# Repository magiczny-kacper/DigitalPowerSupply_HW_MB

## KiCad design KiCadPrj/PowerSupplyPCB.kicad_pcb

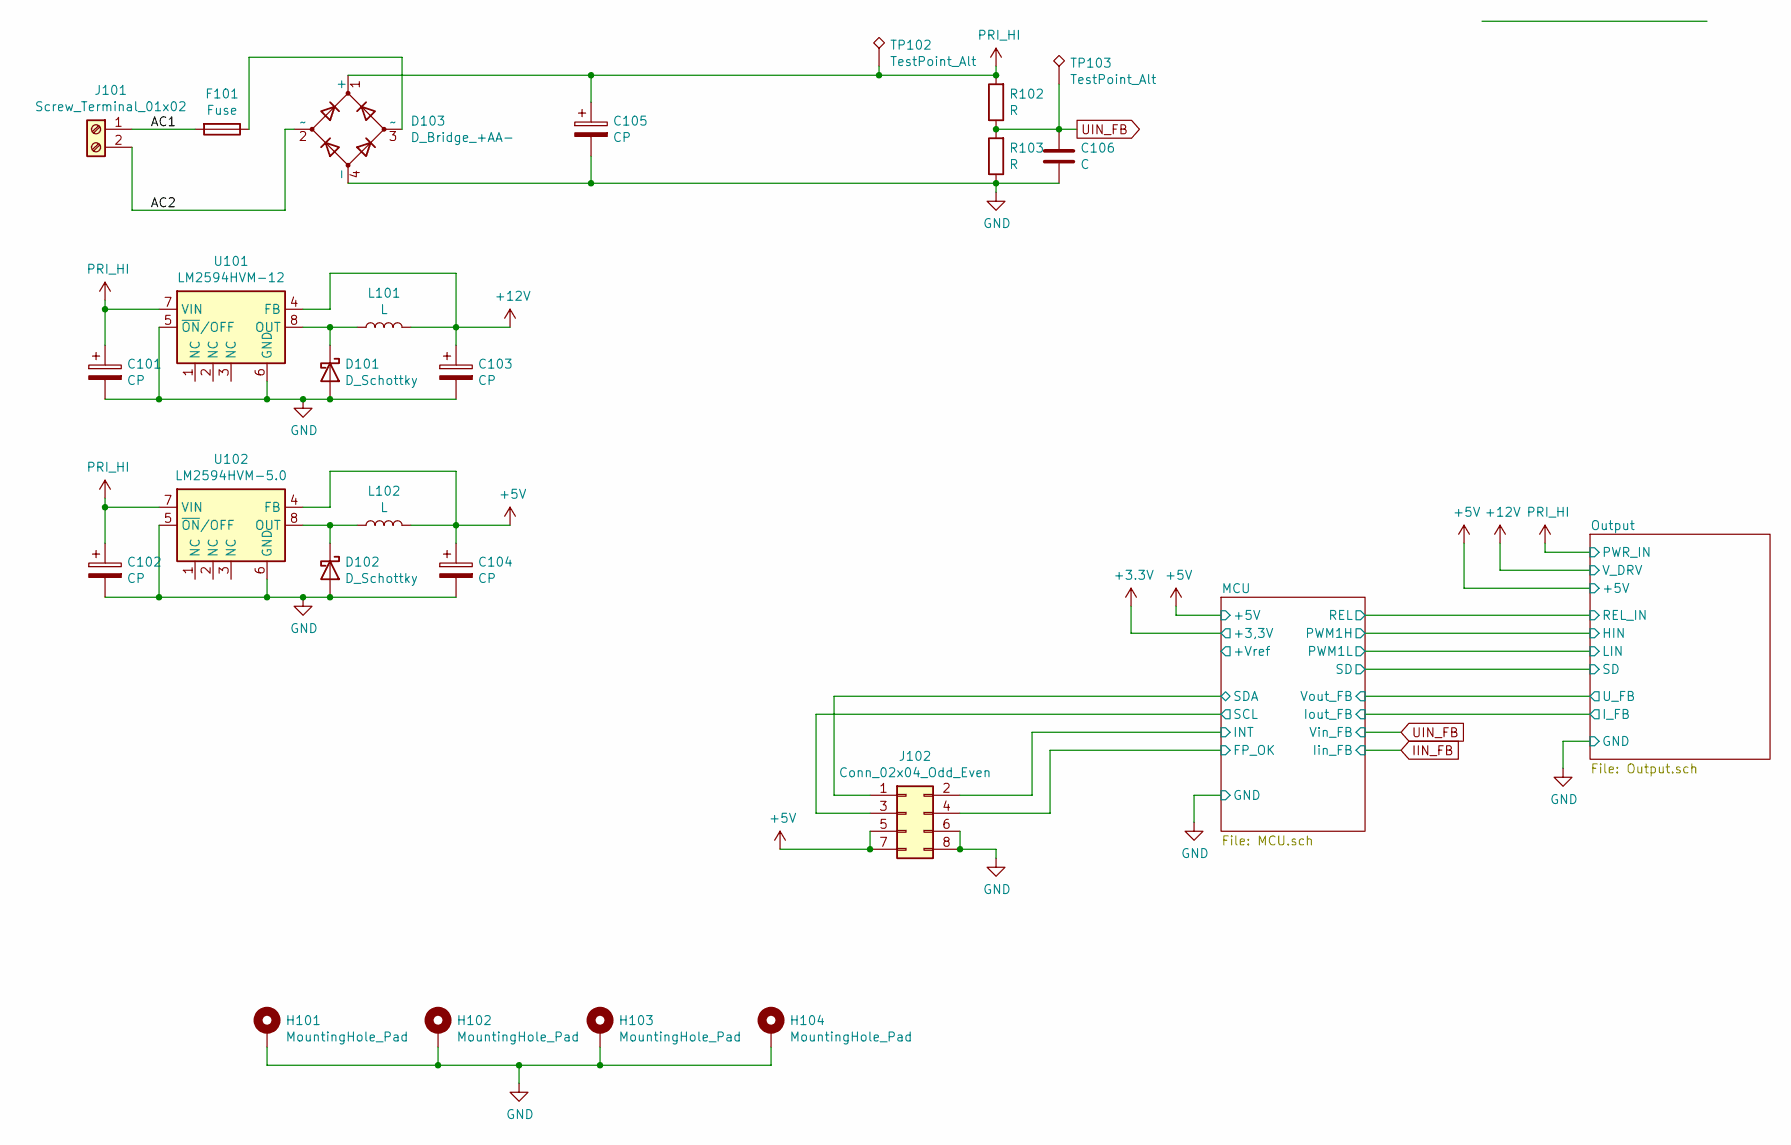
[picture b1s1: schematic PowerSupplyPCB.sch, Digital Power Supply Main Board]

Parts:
C101, C102, C103, C104: CP; CP_Elec_5x3.9
C105: CP; CP_Radial_D22.0mm_P10.00mm_SnapIn
C106: C; C_0805_2012Metric
D101, D102: D_Schottky; D_SMA
D103: D_Bridge_+AA-; Diode_Bridge_Vishay_KBU
F101: Fuse; Fuseholder_Cylinder-5x20mm_EATON_HBW_Vertical_Closed
H101, H102, H103, H104: MountingHole_Pad; MountingHole_3.2mm_M3_Pad_Via
J101: Screw_Terminal_01x02; PhoenixContact_MSTBVA_2,5_2-G-5,08_1x02_P5.08mm_Vertical
J102: Conn_02x04_Odd_Even; IDC-Header_2x04_P2.54mm_Vertical
L101, L102: L; L_Bourns_SRN8040TA
R102, R103: R; R_0805_2012Metric
TP102, TP103: TestPoint_Alt; TestPoint_Pad_3.0x3.0mm
U101: LM2594HVM-12; SOIC-8_3.9x4.9mm_P1.27mm
U102: LM2594HVM-5.0; SOIC-8_3.9x4.9mm_P1.27mm

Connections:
+5V: C104.1, J102.5, J102.7, L102.2, U102.4 (FB); also elsewhere on the board
+12V: C103.1, L101.2, U101.4 (FB); also elsewhere on the board
/AC1: F101.2, J101.1
/AC2: D103.2 (~~), J101.2
/MCU/FP_OK: J102.4; also elsewhere on the board
/MCU/INT: J102.2; also elsewhere on the board
/MCU/SCL: J102.3; also elsewhere on the board
/MCU/SDA: J102.1; also elsewhere on the board
GND: C101.2, C102.2, C103.2, C104.2, C105.2, C106.1, D101.2 (A), D102.2 (A), D103.4 (-), H101.1, H102.1, H103.1, H104.1, J102.6, J102.8, R103.1, U101.5 (~ON~/OFF), U101.6 (GND), U102.5 (~ON~/OFF), U102.6 (GND); also elsewhere on the board
unnamed: D101.1 (K), L101.1, U101.8 (OUT)
unnamed: D102.1 (K), L102.1, U102.8 (OUT)
unnamed: D103.3 (~~), F101.1
PRI_HI: C101.1, C102.1, C105.1, D103.1 (+), R102.2, TP102.1, U101.7 (VIN), U102.7 (VIN); also elsewhere on the board
UIN_FB: C106.2, R102.1, R103.2, TP103.1; also elsewhere on the board

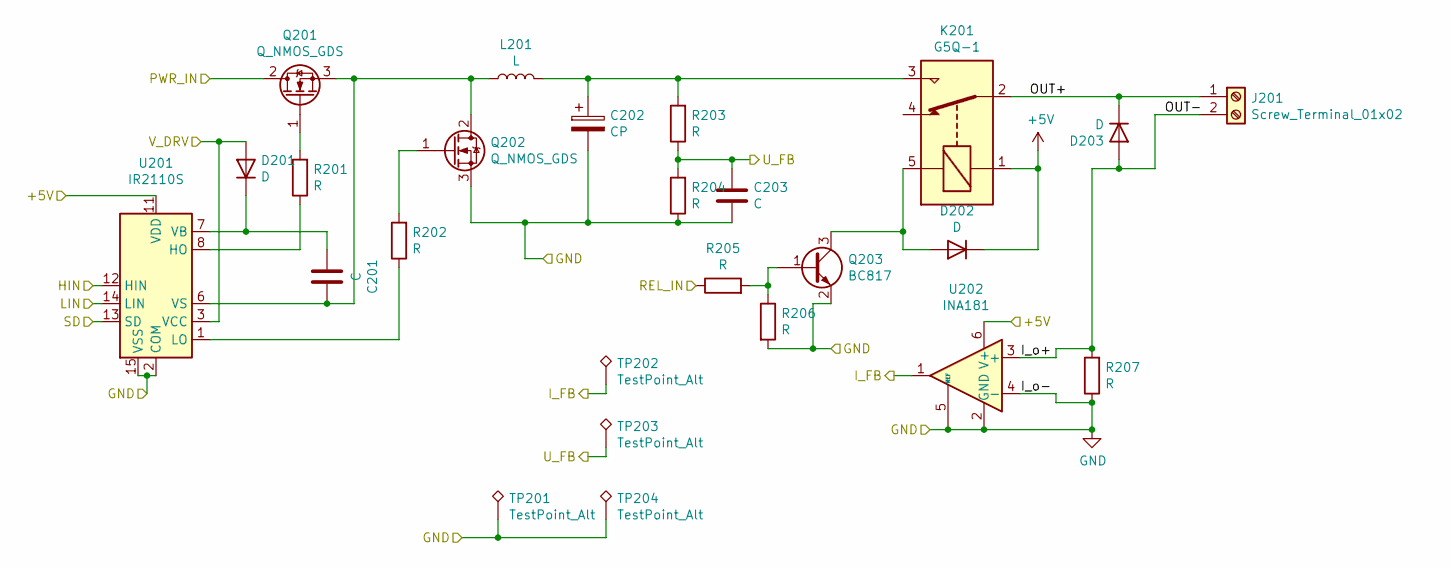
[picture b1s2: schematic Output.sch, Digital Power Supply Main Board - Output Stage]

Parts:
C201, C203: C; C_0805_2012Metric
C202: CP; CP_Radial_D22.0mm_P10.00mm_SnapIn
D201, D202, D203: D; D_SMA
J201: Screw_Terminal_01x02; PhoenixContact_MSTBVA_2,5_2-G-5,08_1x02_P5.08mm_Vertical
K201: G5Q-1; Relay_SPDT_Omron-G5Q-1
L201: L; WE_74437529203331
Q201, Q202: Q_NMOS_GDS; TO-220-3_Vertical
Q203: BC817; SOT-23
R201, R202, R203, R204, R205, R206: R; R_0805_2012Metric
R207: R; R_2512_6332Metric
TP201, TP202, TP203, TP204: TestPoint_Alt; TestPoint_Pad_3.0x3.0mm
U201: IR2110S; SOIC-16W_7.5x10.3mm_P1.27mm
U202: INA181; SOT-23-6

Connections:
+5V: D202.1 (K), K201.1, U201.11 (VDD), U202.6 (V+); also elsewhere on the board
+12V: D201.2 (A), U201.3 (VCC); also elsewhere on the board
/MCU/REL: R205.1; also elsewhere on the board
/MCU/SD: U201.13 (SD); also elsewhere on the board
/Output/HIN: U201.12 (HIN); also elsewhere on the board
/Output/I_FB: TP202.1, U202.1; also elsewhere on the board
/Output/I_o+: D203.2 (A), J201.2, R207.2, U202.3 (+)
/Output/LIN: U201.14 (LIN); also elsewhere on the board
/Output/OUT+: D203.1 (K), J201.1, K201.2
/Output/U_FB: C203.2, R203.1, R204.2, TP203.1; also elsewhere on the board
GND: C202.2, C203.1, Q202.3 (S), Q203.2 (E), R204.1, R206.2, R207.1, TP201.1, TP204.1, U201.2 (COM), U201.15 (VSS), U202.2 (GND), U202.4 (-), U202.5 (REF); also elsewhere on the board
unnamed: C201.1, L201.1, Q201.3 (S), Q202.2 (D), U201.6 (VS)
unnamed: C201.2, D201.1 (K), U201.7 (VB)
unnamed: C202.1, K201.3, L201.2, R203.2
unnamed: D202.2 (A), K201.5, Q203.3 (C)
unnamed: Q201.1 (G), R201.2
unnamed: Q202.1 (G), R202.2
unnamed: Q203.1 (B), R205.2, R206.1
unnamed: R201.1, U201.8 (HO)
unnamed: R202.1, U201.1 (LO)
PRI_HI: Q201.2 (D); also elsewhere on the board

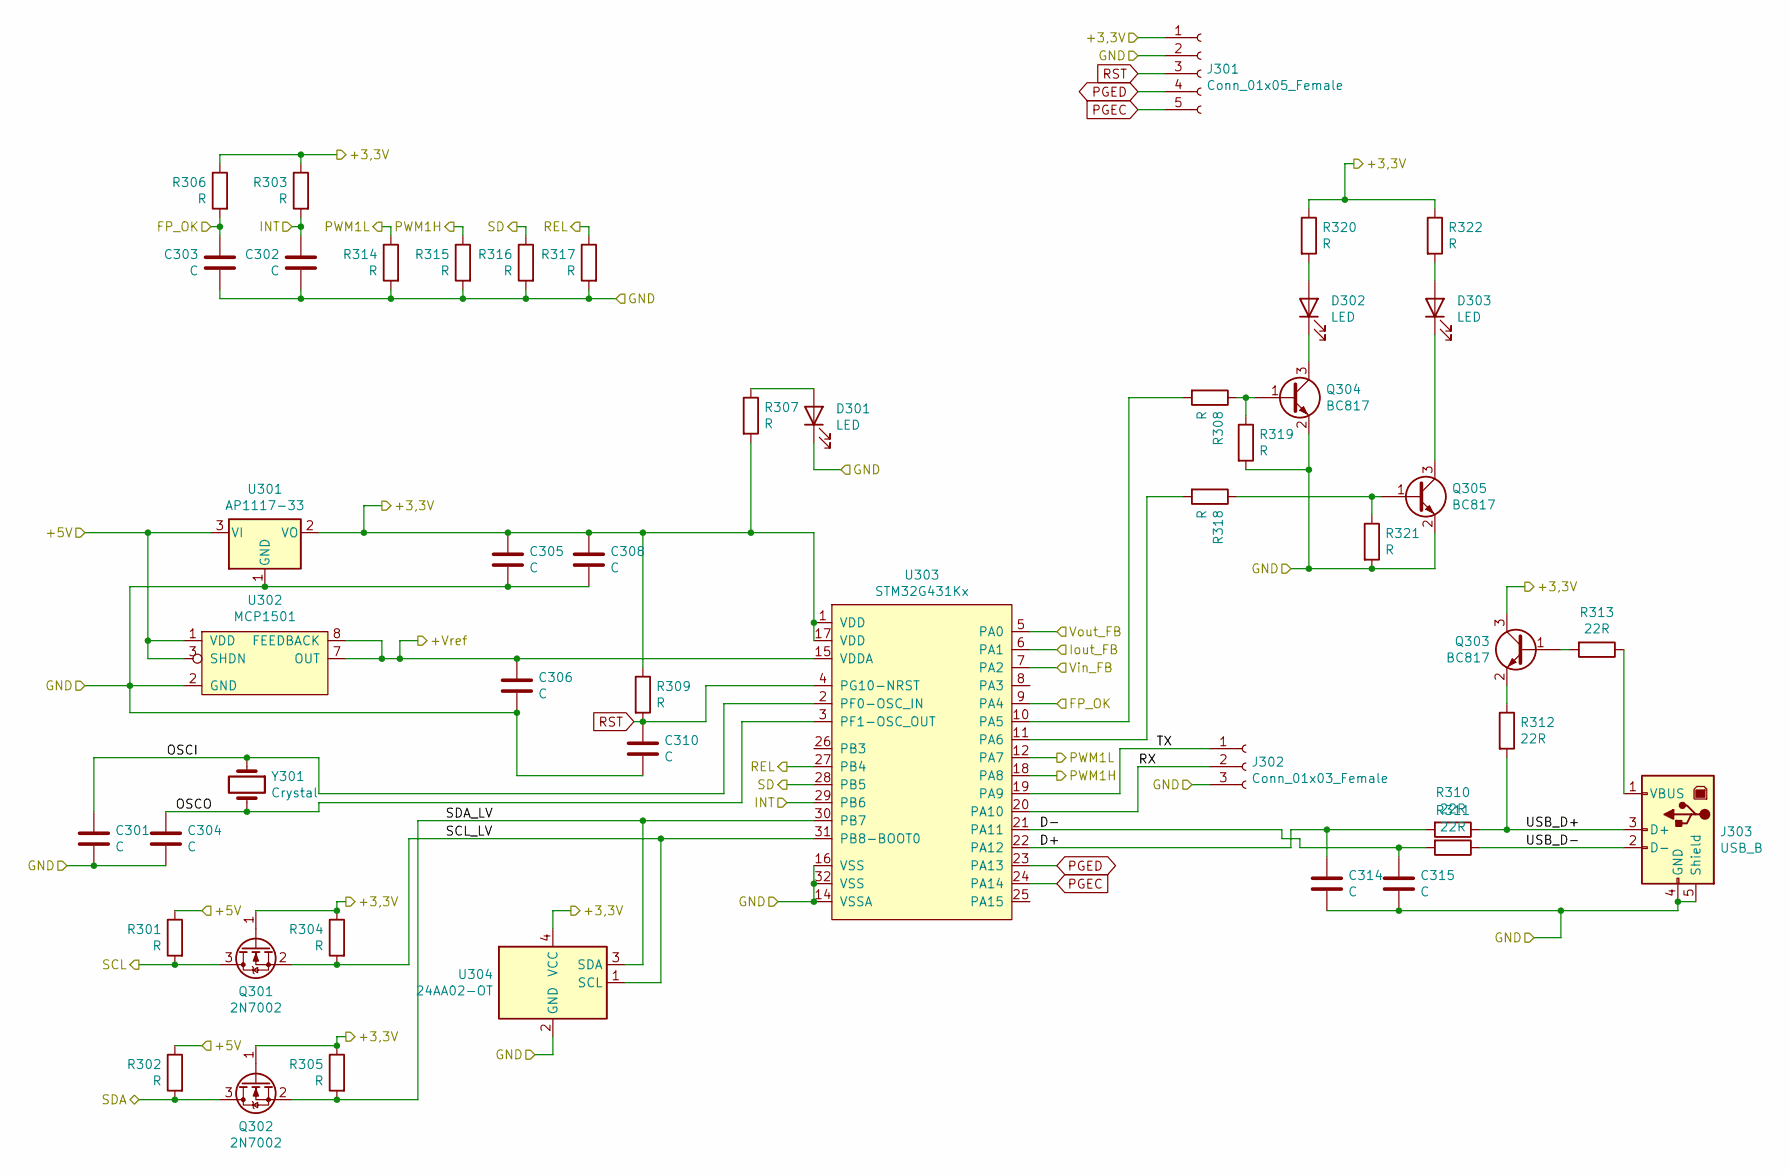
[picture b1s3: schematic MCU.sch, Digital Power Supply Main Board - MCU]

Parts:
C301, C302, C303, C304, C305, C306, C308, C310, C314, C315: C; C_0805_2012Metric
D301, D302, D303: LED; LED_0805_2012Metric
J301: Conn_01x05_Female; PinSocket_1x05_P2.54mm_Vertical
J302: Conn_01x03_Female; PinSocket_1x03_P2.54mm_Vertical
J303: USB_B; USB_B_Lumberg_2411_02_Horizontal
Q301, Q302: 2N7002; SOT-23
Q303, Q304, Q305: BC817; SOT-23
R301, R302, R303, R304, R305, R306, R307, R308, R309, R314, R315, R316, R317, R318, R319, R320, R321, R322: R; R_0805_2012Metric
R310, R311, R312, R313: 22R; R_0805_2012Metric
U301: AP1117-33; SOT-223-3_TabPin2
U302: MCP1501; SOIC-8_3.9x4.9mm_P1.27mm
U303: STM32G431Kx; LQFP-32_7x7mm_P0.8mm
U304: 24AA02-OT; SOT-23-5
Y301: Crystal; Crystal_HC49-4H_Vertical

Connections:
+3V3: C305.1, C308.1, J301.1, Q301.1 (G), Q302.1 (G), Q303.3 (C), R303.1, R304.1, R305.1, R306.1, R307.2, R309.1, R320.1, R322.1, U301.2 (VO), U303.1 (VDD), U303.17 (VDD), U304.4 (VCC)
+5V: R301.1, R302.1, U301.3 (VI), U302.1 (VDD), U302.3 (SHDN); also elsewhere on the board
/MCU/+Vref: C306.1, U302.7 (OUT), U302.8 (FEEDBACK), U303.15 (VDDA)
/MCU/D+: C314.1, R310.2, U303.22 (PA12)
/MCU/D-: C315.1, R311.2, U303.21 (PA11)
/MCU/FP_OK: C303.1, R306.2, U303.9 (PA4); also elsewhere on the board
/MCU/INT: C302.1, R303.2, U303.29 (PB6); also elsewhere on the board
/MCU/OSCI: C301.1, U303.2 (PF0-OSC_IN), Y301.1
/MCU/OSCO: C304.1, U303.3 (PF1-OSC_OUT), Y301.2
/MCU/REL: R317.1, U303.27 (PB4); also elsewhere on the board
/MCU/RX: J302.2, U303.20 (PA10)
/MCU/SCL: Q301.3 (D), R301.2; also elsewhere on the board
/MCU/SCL_LV: Q301.2 (S), R304.2, U303.31 (PB8-BOOT0), U304.1 (SCL)
/MCU/SD: R316.1, U303.28 (PB5); also elsewhere on the board
/MCU/SDA: Q302.3 (D), R302.2; also elsewhere on the board
/MCU/SDA_LV: Q302.2 (S), R305.2, U303.30 (PB7), U304.3 (SDA)
/MCU/TX: J302.1, U303.19 (PA9)
/MCU/USB_D+: J303.3 (D+), R310.1, R312.2
/MCU/USB_D-: J303.2 (D-), R311.1
/Output/HIN: R315.1, U303.18 (PA8); also elsewhere on the board
/Output/I_FB: U303.6 (PA1); also elsewhere on the board
/Output/LIN: R314.1, U303.12 (PA7); also elsewhere on the board
/Output/U_FB: U303.5 (PA0); also elsewhere on the board
GND: C301.2, C302.2, C303.2, C304.2, C305.2, C306.2, C308.2, C310.2, C314.2, C315.2, D301.1 (K), J301.2, J302.3, J303.4 (GND), J303.5 (Shield), Q304.2 (E), Q305.2 (E), R314.2, R315.2, R316.2, R317.2, R319.2, R321.2, U301.1 (GND), U302.2 (GND), U302.4 (GND), U302.5 (GND), U302.6 (GND), U303.14 (VSSA), U303.16 (VSS), U303.32 (VSS), U304.2 (GND); also elsewhere on the board
unnamed: D301.2 (A), R307.1
unnamed: D302.1 (K), Q304.3 (C)
unnamed: D302.2 (A), R320.2
unnamed: D303.1 (K), Q305.3 (C)
unnamed: D303.2 (A), R322.2
unnamed: J303.1 (VBUS), R313.1
unnamed: Q303.1 (B), R313.2
unnamed: Q303.2 (E), R312.1
unnamed: Q304.1 (B), R308.1, R319.1
unnamed: Q305.1 (B), R318.1, R321.1
unnamed: R308.2, U303.10 (PA5)
unnamed: R318.2, U303.11 (PA6)
PGEC: J301.5, U303.24 (PA14)
PGED: J301.4, U303.23 (PA13)
RST: C310.1, J301.3, R309.2, U303.4 (PG10-NRST)
UIN_FB: U303.7 (PA2); also elsewhere on the board

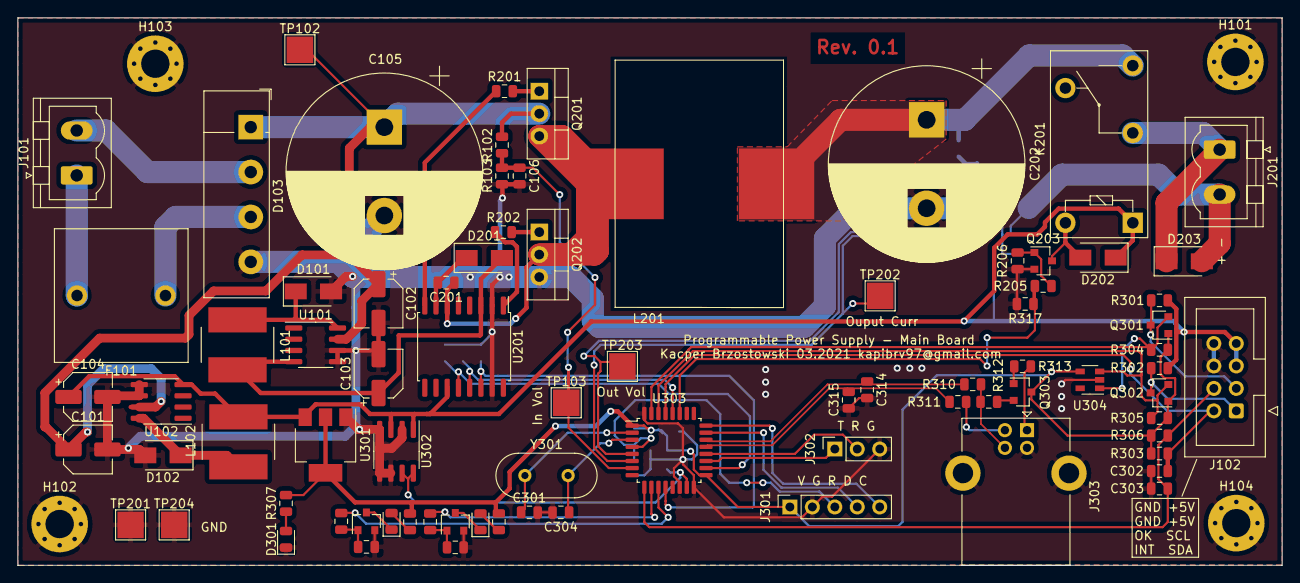
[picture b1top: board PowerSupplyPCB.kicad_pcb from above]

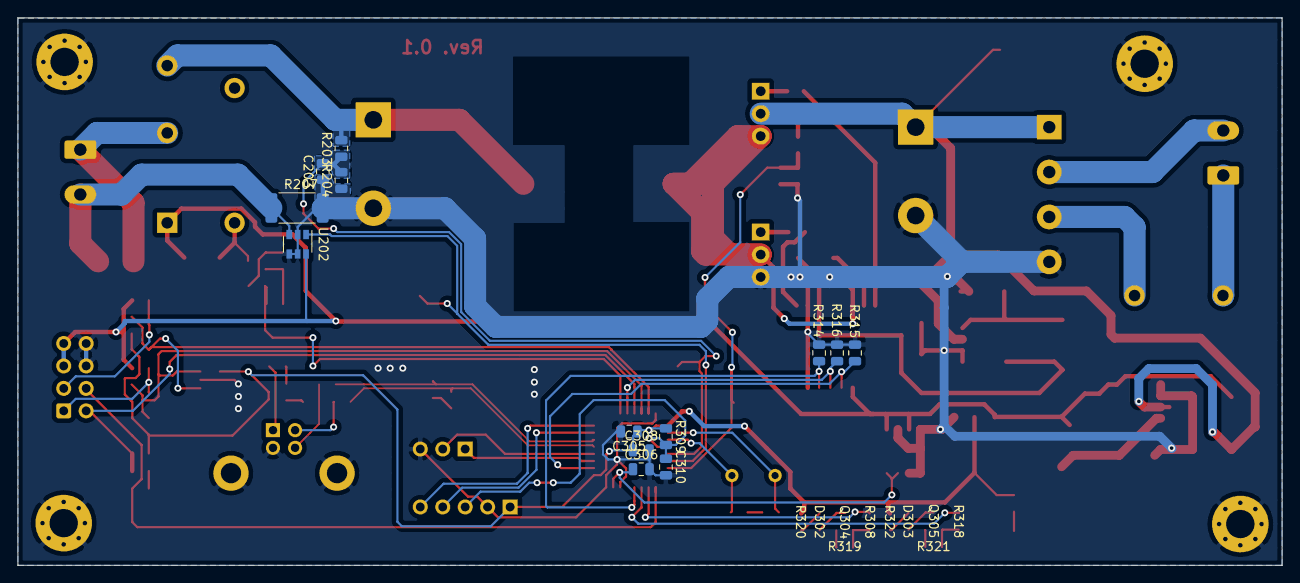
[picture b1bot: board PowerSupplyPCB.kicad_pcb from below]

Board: 2 copper layers, 143.0 x 61.9 mm, 97 parts (13 on the bottom side), 58 nets.

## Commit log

2021-05-25 Changed file structure
2021-05-26 Updated PDF
2021-05-26 Added production files
2021-05-26 Minor changes
